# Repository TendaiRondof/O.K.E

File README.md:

# O.K.E
Bereichs übergreifendes Projekt (Optische Kontroll Einheit)

Robo_arm grid = 0.1mm x/Y

cam grid=	0.33mmx
		0.247mmy

Wenn nöd teil vo dem bisch... was machsch den da?

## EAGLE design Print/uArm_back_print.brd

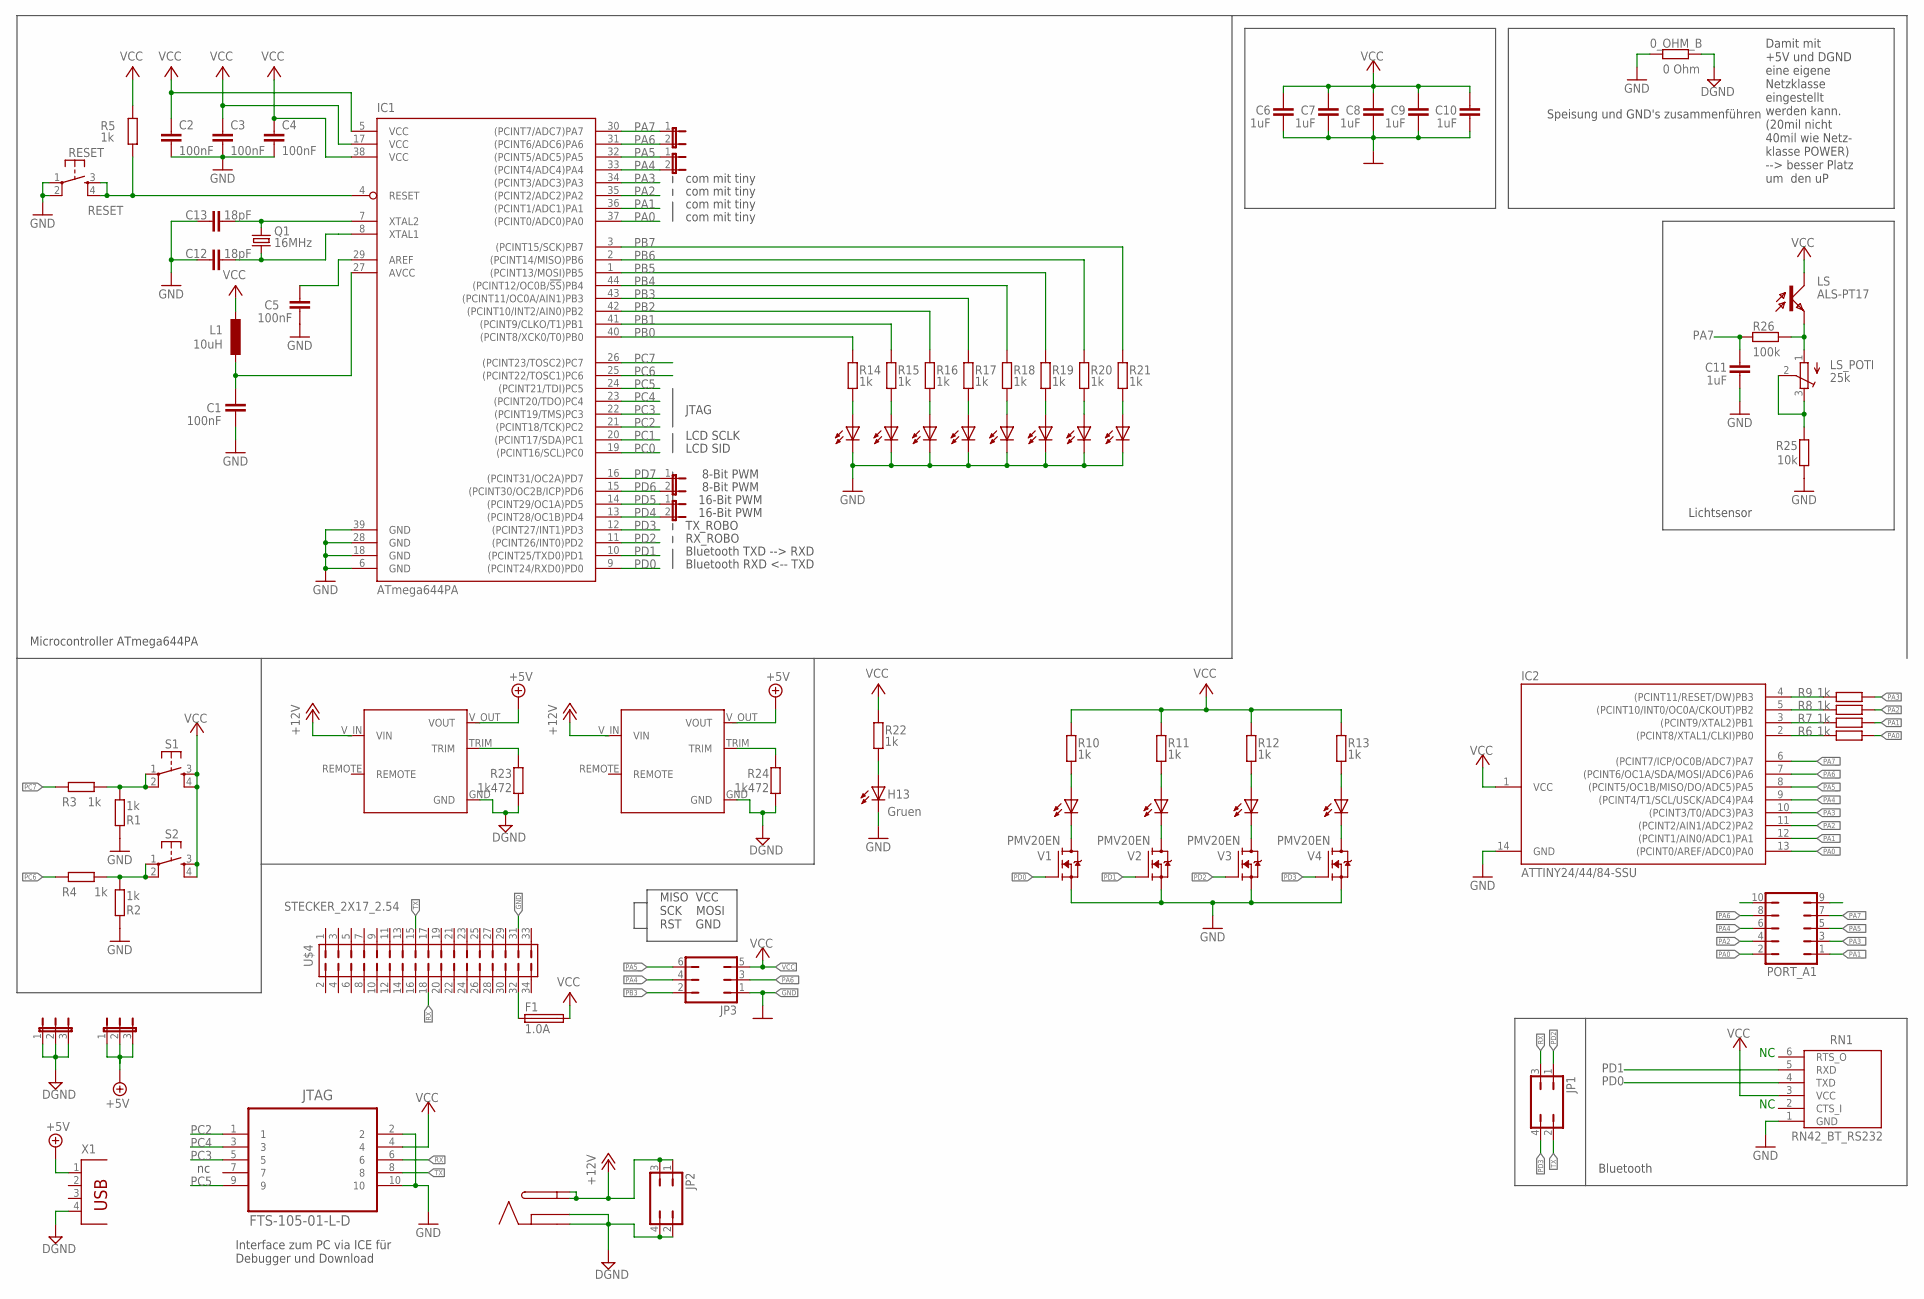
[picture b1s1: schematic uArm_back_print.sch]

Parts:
0_OHM_B: 0 Ohm; R0805
C1, C2, C3, C4, C5: 100nF; C0805
C6, C7, C8, C9, C10, C11: 1uF; C0805
C12, C13: 18pF; C0805
F1: 1.0A; F1206
H1, H2, H3, H4, H5, H6, H7, H8, H9, H10, H11, H12, H13: Gruen; CHIPLED_1206
IC1: ATmega644PA; TQFP44
IC2: ATTINY24/44/84-SSU; SOIC14
IC3, IC4: DCDC; 1X2,3_2.54MM
JP1, JP2: JP2Q
JP3: JP3Q
JP4, JP5, JP8, JP9: JP1
JP6, JP7: JP2E; JP2
JTAG: FTS-105-01-L-D; SAMTEC_FTS-105-01-L-D
L1: 10uH; L2825P
LS: ALS-PT17; SOD232-W
LS_POTI: 25k; 3223G
PORT_A1: JP5Q
Q1: 16MHz; HC49UP
R1, R2, R3, R4, R5, R6, R7, R8, R9, R10, R11, R12, R13, R14, R15, R16, R17, R18, R19, R20, R21, R22: 1k; R0805
R23, R24: 1k472; R0805
R25: 10k; R0805
R26: 100k; R0805
RESET: TS42_4PAD
RN1: RN42_BT_RS232; RN42BT_RS232
S1, S2: TS42_4PAD
U$1: BUCHSE
U$4: STECKER_2X17_2.54; 2X17_2.54
V1, V2, V3, V4: PMV20EN; SOT23
X1: PN87520

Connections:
+5V: IC3.V_OUT (VOUT), IC4.V_OUT (VOUT), JP6.1, JP6.2, JP6.3, X1.1
+12V: IC3.V_IN (VIN), IC4.V_IN (VIN), JP2.1, JP2.3, U$1.3, U$1.3.1
DGND: 0_OHM_B.2, IC3.GND, IC4.GND, JP2.2, JP2.4, JP7.1, JP7.2, JP7.3, R23.1, R24.1, U$1.1, U$1.2, X1.4
GND: 0_OHM_B.1, C1.1, C2.2, C3.2, C4.2, C5.1, C6.1, C7.1, C8.1, C9.1, C10.1, C11.1, C12.2, C13.1, H1.C, H2.C, H3.C, H4.C, H5.C, H6.C, H7.C, H8.C, H13.C, IC1.6 (GND), IC1.18 (GND), IC1.28 (GND), IC1.39 (GND), IC2.14 (GND), JP3.1, JTAG.2, JTAG.10, R1.1, R2.1, R25.1, RESET.1, RESET.2, RN1.1 (GND), U$4.31, V1.2 (S), V2.2 (S), V3.2 (S), V4.2 (S)
unnamed: F1.1, U$4.32
unnamed: H10.C, V2.3 (D)
unnamed: H9.C, V1.3 (D)
unnamed: H10.A, R11.1
unnamed: H9.A, R10.1
unnamed: LS.E, LS_POTI.1 (A), R26.2
unnamed: LS_POTI.2 (S), LS_POTI.3 (E), R25.2
unnamed: H12.C, V4.3 (D)
unnamed: H1.A, R14.1
unnamed: H12.A, R13.1
unnamed: H11.A, R12.1
unnamed: H11.C, V3.3 (D)
unnamed: H2.A, R15.1
unnamed: H3.A, R16.1
unnamed: IC3.TRIM, R23.2
unnamed: H4.A, R17.1
unnamed: H5.A, R18.1
unnamed: H6.A, R19.1
unnamed: H7.A, R20.1
unnamed: R1.2, R3.2, S1.1, S1.2
unnamed: R2.2, R4.2, S2.1, S2.2
unnamed: H8.A, R21.1
unnamed: C1.2, IC1.27 (AVCC), L1.2
unnamed: C12.1, IC1.8 (XTAL1), Q1.1
unnamed: C13.2, IC1.7 (XTAL2), Q1.2
unnamed: C5.2, IC1.29 (AREF)
unnamed: H13.A, R22.1
unnamed: IC4.TRIM, R24.2
PA0: IC1.37 ((PCINT0/ADC0)PA0), R6.1
PA0_: IC2.13 ((PCINT0/AREF/ADC0)PA0), PORT_A1.2
PA1: IC1.36 ((PCINT1/ADC1)PA1), R7.1
PA1_: IC2.12 ((PCINT1/AIN0/ADC1)PA1), PORT_A1.1
PA2: IC1.35 ((PCINT2/ADC2)PA2), R8.1
PA2_: IC2.11 ((PCINT2/AIN1/ADC2)PA2), PORT_A1.4
PA3: IC1.34 ((PCINT3/ADC3)PA3), R9.1
PA3_: IC2.10 ((PCINT3/T0/ADC3)PA3), PORT_A1.3
PA4: IC1.33 ((PCINT4/ADC4)PA4), JP9.2
PA4_: IC2.9 ((PCINT4/T1/SCL/USCK/ADC4)PA4), JP3.4, PORT_A1.6
PA5: IC1.32 ((PCINT5/ADC5)PA5), JP9.1
PA5_: IC2.8 ((PCINT5/OC1B/MISO/DO/ADC5)PA5), JP3.6, PORT_A1.5
PA6: IC1.31 ((PCINT6/ADC6)PA6), JP8.2
PA6_: IC2.7 ((PCINT6/OC1A/SDA/MOSI/ADC6)PA6), JP3.3, PORT_A1.8
PA7: C11.2, IC1.30 ((PCINT7/ADC7)PA7), JP8.1, R26.1
PA7_: IC2.6 ((PCINT7/ICP/OC0B/ADC7)PA7), PORT_A1.7
PB0: IC1.40 ((PCINT8/XCK0/T0)PB0), R14.2
PB0_: IC2.2 ((PCINT8/XTAL1/CLKI)PB0), R6.2
PB1: IC1.41 ((PCINT9/CLKO/T1)PB1), R15.2
PB1_: IC2.3 ((PCINT9/XTAL2)PB1), R7.2
PB2: IC1.42 ((PCINT10/INT2/AIN0)PB2), R16.2
PB2_: IC2.5 ((PCINT10/INT0/OC0A/CKOUT)PB2), R8.2
PB3: IC1.43 ((PCINT11/OC0A/AIN1)PB3), R17.2
PB3_: IC2.4 ((PCINT11/RESET/DW)PB3), JP3.2, R9.2
PB4: IC1.44 ((PCINT12/OC0B/!SS!)PB4), R18.2
PB5: IC1.1 ((PCINT13/MOSI)PB5), R19.2
PB6: IC1.2 ((PCINT14/MISO)PB6), R20.2
PB7: IC1.3 ((PCINT15/SCK)PB7), R21.2
PC0: IC1.19 ((PCINT16/SCL)PC0)
PC1: IC1.20 ((PCINT17/SDA)PC1)
PC2: IC1.21 ((PCINT18/TCK)PC2), JTAG.1
PC3: IC1.22 ((PCINT19/TMS)PC3), JTAG.5
PC4: IC1.23 ((PCINT20/TDO)PC4), JTAG.3
PC5: IC1.24 ((PCINT21/TDI)PC5), JTAG.9
PC6: IC1.25 ((PCINT22/TOSC1)PC6), R4.1
PC7: IC1.26 ((PCINT23/TOSC2)PC7), R3.1
PD0: IC1.9 ((PCINT24/RXD0)PD0), RN1.4 (TXD), V1.1 (G)
PD1: IC1.10 ((PCINT25/TXD0)PD1), RN1.5 (RXD), V2.1 (G)
PD2: IC1.11 ((PCINT26/INT0)PD2), JP1.1, V3.1 (G)
PD3: IC1.12 ((PCINT27/INT1)PD3), JP1.4, V4.1 (G)
PD4: IC1.13 ((PCINT28/OC1B)PD4), JP4.2
PD5: IC1.14 ((PCINT29/OC1A)PD5), JP4.1
PD6: IC1.15 ((PCINT30/OC2B/ICP)PD6), JP5.2
PD7: IC1.16 ((PCINT31/OC2A)PD7), JP5.1
RESET: IC1.4 (RESET), R5.1, RESET.3, RESET.4
RX: JP1.3, JTAG.6, U$4.18
TX: JP1.2, JTAG.8, U$4.15
VCC: C2.1, C3.1, C4.1, C6.2, C7.2, C8.2, C9.2, C10.2, F1.2, IC1.5 (VCC), IC1.17 (VCC), IC1.38 (VCC), IC2.1 (VCC), JP3.5, JTAG.4, L1.1, LS.C, R5.2, R10.2, R11.2, R12.2, R13.2, R22.2, RN1.3 (VCC), S1.3, S1.4, S2.3, S2.4

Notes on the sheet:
JTAG
16-Bit PWM
8-Bit PWM
Interface zum PC via ICE für Debugger und Download
Microcontroller ATmega644PA
LCD SID
LCD SCLK
Bluetooth
Bluetooth RXD <-- TXD
Bluetooth TXD --> RXD
Speisung und GND's zusammenführen
Damit mit +5V und DGND eine eigene Netzklasse eingestellt werden kann. (20mil nicht 40mil wie Netz- klasse POWER) --> besser Platz um den uP
RX_ROBO
TX_ROBO
com mit tiny
MISO VCC SCK MOSI RST GND
Lichtsensor

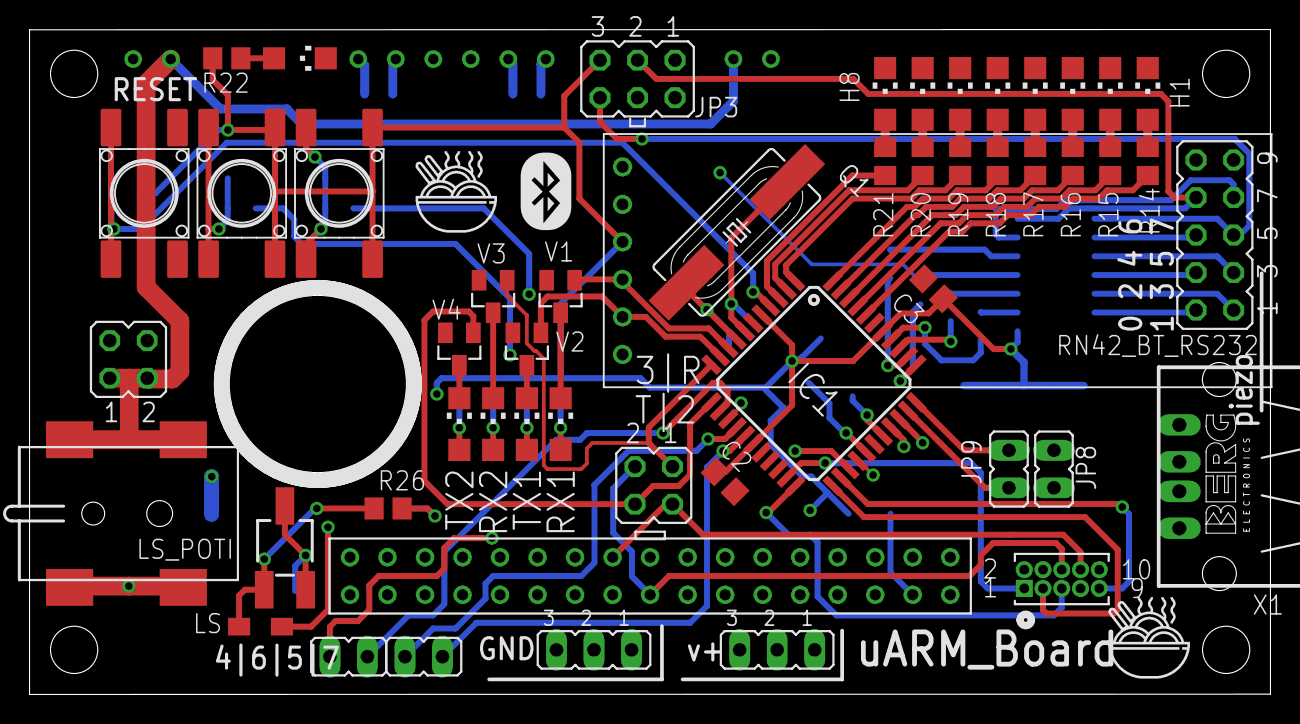
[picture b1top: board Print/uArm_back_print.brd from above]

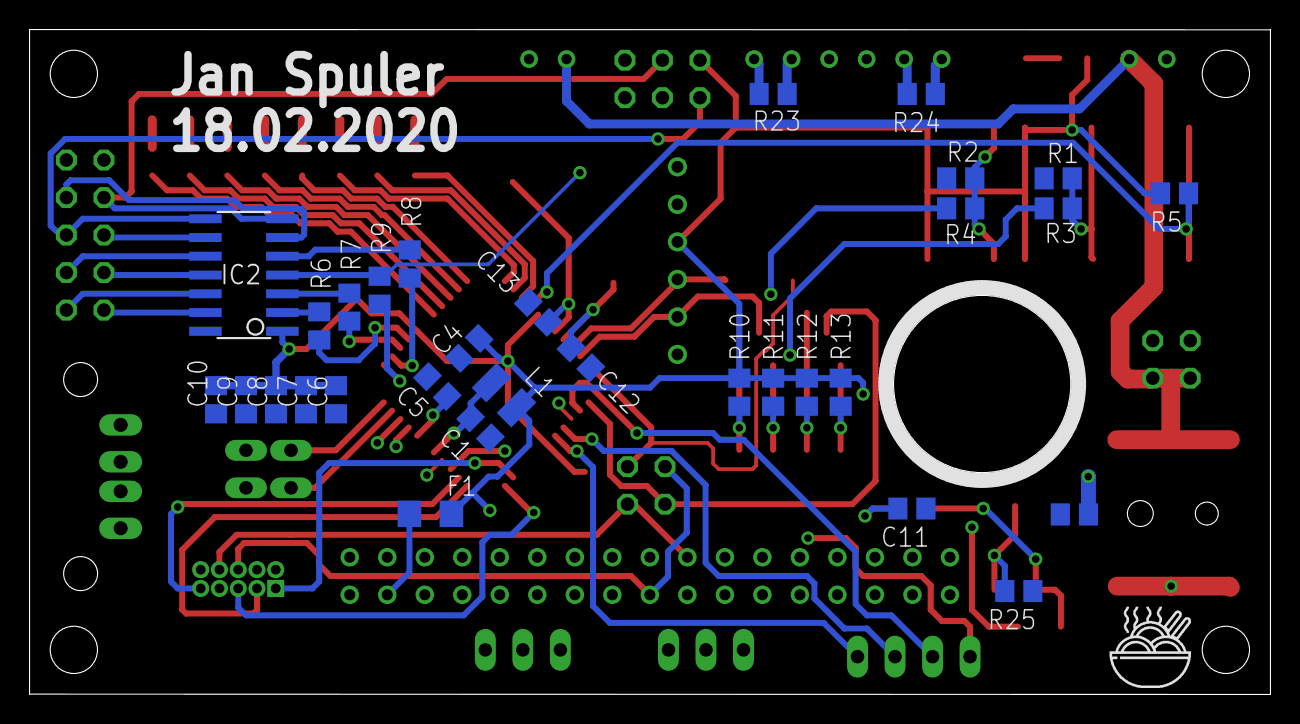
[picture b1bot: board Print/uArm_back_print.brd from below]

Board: 4 copper layers, 84.0 x 45.0 mm, 84 parts (31 on the bottom side), 78 nets.

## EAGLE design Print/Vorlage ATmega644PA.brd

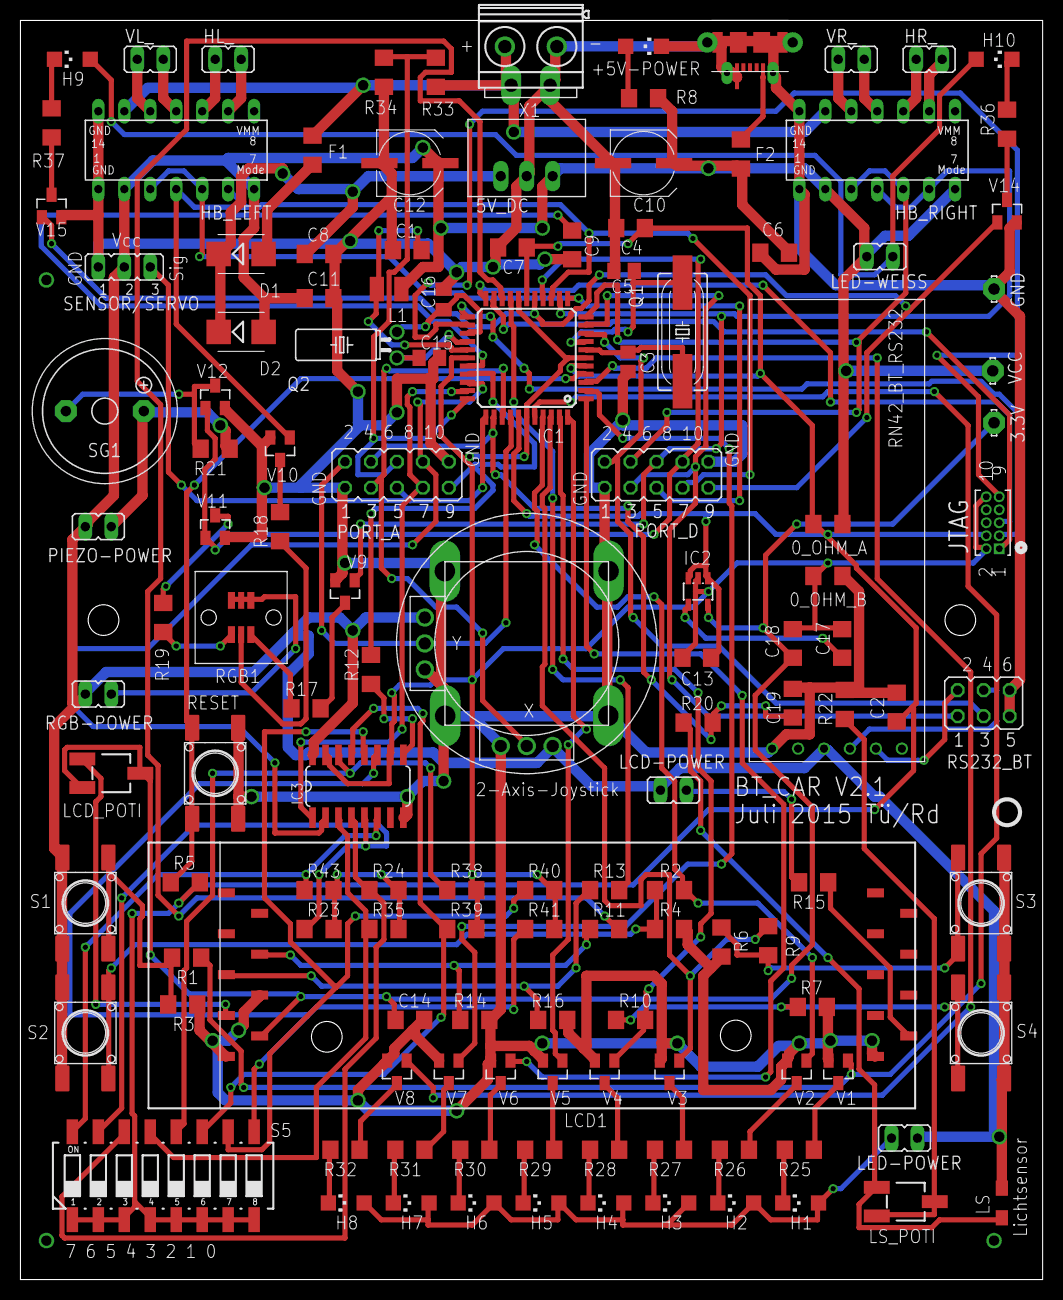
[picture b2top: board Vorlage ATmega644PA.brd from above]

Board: 2 copper layers, 100.0 x 123.2 mm, 134 parts (0 on the bottom side), 109 nets.

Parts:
0_OHM_A, 0_OHM_B: 0 Ohm; R1206
3.3V: 3.3V; LSP11
5V_DC: RECOM_DCDC
+5V-POWER: Gruen; CHIPLED_1206
C1, C2, C4, C6, C7, C8, C9, C11, C14, C17: 100nF; C1206
C3: 18pF; C0805
C5: 18pF; C0805K
C10, C12: 100uF; UD-6,3X5,8_NICHICON
C13, C18, C19: 1uF; C1206
C15, C16: 12pF; C0805K
D1, D2: MBRS130LT3; SMB
F1: 1.0A; F1206
F2: 500mA; F1206
GND: 3.3V; LSP11
H1, H3, H5, H7: rot; CHIPLED_1206
H2, H4, H6, H8: blau; CHIPLED_1206
H9, H10: weiss; CHIPLED_1206
HB_LEFT: DRV8835; DIL14
HB_RIGHT: DRV8835; DIL14
HL_: JP1
HR_: JP1
IC1: ATmega644PA; TQFP44
IC2: LP2985-XXDBVR; SOT23-DBV
IC3: 74AC165D; SO16
JTAG: FTS-105-01-L-D; SAMTEC_FTS-105-01-L-D
L1: 10uH; L2825P
LCD1: EADIP203-4_SMD; EADIP203-4SMD
LCD-POWER: JP1
LCD_POTI: 2k5; 3223G
LED-POWER: JP1
LED-WEISS: JP1
LS: ALS-PT17; SOD232-W
LS_POTI: 25k; 3223G
PIEZO-POWER: JP1
PORT_A: JP5Q
PORT_D: JP5Q
Q1: 16MHz; HC49UP
Q2: 32.768kHz; TC38H
R1, R2, R8, R9, R10, R11, R12, R13, R21: 1k; R1206
R3, R4, R6, R7, R20, R23, R24, R33, R34, R35, R38, R39, R40, R41, R43: 100k; R1206
R5, R22: 10k; R1206
R14, R16: 2k; R1206
R15, R17, R18, R19, R25, R26, R27, R28, R29, R30, R31, R32, R36, R37: 150R; R1206
RESET: TS42_4PAD
RGB1: LED_MIT_DIFUSOR
RGB-POWER: JP1
RN1: RN42_BT_RS232; RN42BT_RS232
RS232_BT: JP3Q
S1, S2, S3, S4: TS42_4PAD
S5: 219-08; CTS-219-08
SENSOR/SERVO: JP2
SG1: F/TMB
U$1: MICRO-USB; 47589-0001
U$6: 2-AXIS-JOYSTICK
V1, V2, V3, V4, V5, V6, V7, V8, V9, V10, V11, V12, V14, V15: PMV20EN; SOT23
VCC: 3.3V; LSP11
VL_: JP1
VR_: JP1
X1: MKDSN1,5/2-5,08

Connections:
3.3V: 3.3V.MP, C14.1, C18.1, IC2.5, LCD1.2, LCD_POTI.2, LCD_POTI.3
+5V: 0_OHM_A.2, C2.1, C4.1, C7.1, C13.1, IC1.5, IC1.17, IC1.38, IC2.1, IC2.3, JTAG.4, R5.2, S5.1, S5.2, S5.3, S5.4, S5.5, S5.6, S5.7, S5.8
DGND: 0_OHM_B.2, C13.2, C17.2, C18.2, IC1.6, IC1.18, IC1.28, IC1.39, IC2.2, IC3.10, IC3.15, JTAG.2, JTAG.10, R23.2, R24.2, R35.2, R38.2, R39.2, R40.2, R41.2, R43.2
GND: 0_OHM_B.1, 5V_DC.GND, +5V-POWER.C, C1.1, C2.2, C3.1, C4.2, C5.2, C6.2, C7.2, C8.2, C9.1, C10.-, C11.2, C12.-, C14.2, C15.2, C16.2, C19.1, GND.MP, HB_LEFT.1, HB_LEFT.14, HB_RIGHT.1, HB_RIGHT.14, IC3.8, LCD1.1, LCD1.4, LCD1.18, PORT_A.1, PORT_A.10, PORT_D.1, PORT_D.10, R3.1, R4.1, R6.2, R7.2, R14.1, R16.1, R22.1, R34.1, RESET.1, RESET.2, RN1.1, RS232_BT.5, RS232_BT.6, SENSOR/SERVO.1, U$1.5, U$1.CASING1, U$1.CASING2, U$1.CASING3, U$1.CASING4, U$1.CASING5, U$1.CASING6, U$1.CASING7, U$1.CASING8, U$6.CASE1, U$6.CASE2, U$6.CASE3, U$6.CASE4, U$6.L/R-, U$6.U/D-, V1.2, V2.2, V3.2, V4.2, V5.2, V6.2, V7.2, V8.2, V9.2, V10.2, V11.2, V12.2, V14.2, V15.2, X1.1.1, X1.1.2
unnamed: R19.2, RGB1.1
unnamed: R18.2, RGB1.2
unnamed: F2.1, U$1.1
unnamed: H9.A, H10.A, LED-WEISS.2
unnamed: H2.C, R26.2
unnamed: H1.C, R25.2
unnamed: R25.1, V1.3
unnamed: R26.1, V2.3
unnamed: D1.A, F1.2
unnamed: H10.C, R36.2
unnamed: R17.2, RGB1.3
unnamed: LCD-POWER.2, R15.2
unnamed: H1.A, H2.A, H3.A, H4.A, H5.A, H6.A, H7.A, H8.A, LED-POWER.2
unnamed: RN1.5, RS232_BT.2
unnamed: RN1.4, RS232_BT.4
unnamed: R21.2, SG1.-, V12.3
unnamed: IC3.6, R43.1, S5.16
unnamed: IC3.5, R23.1, S5.15
unnamed: LS.E, LS_POTI.1, R20.2
unnamed: LS_POTI.2, LS_POTI.3, R22.2
unnamed: R1.2, R3.2, S1.1, S1.2
unnamed: R2.2, R4.2, S2.1, S2.2
unnamed: R7.1, R10.1, S4.3, S4.4
unnamed: R6.1, R9.1, S3.3, S3.4
unnamed: H4.C, R28.2
unnamed: H3.C, R27.2
unnamed: R17.1, V9.3
unnamed: R18.1, V10.3
unnamed: R19.1, V11.3
unnamed: R27.1, V3.3
unnamed: IC3.4, R24.1, S5.14
unnamed: R28.1, V4.3
unnamed: H9.C, R37.2
unnamed: LCD1.3, LCD_POTI.1
unnamed: C1.2, IC1.27, L1.2
unnamed: C5.1, IC1.8, Q1.1
unnamed: C3.2, IC1.7, Q1.2
unnamed: C9.2, IC1.29
unnamed: LCD1.6, R11.1, R14.2
unnamed: LCD1.5, R13.1, R16.2
unnamed: R37.1, V15.3
unnamed: H6.C, R30.2
unnamed: H5.C, R29.2
unnamed: R29.1, V5.3
unnamed: R30.1, V6.3
unnamed: R36.1, V14.3
unnamed: HB_LEFT.12, VL_.1
unnamed: H8.C, R32.2
unnamed: H7.C, R31.2
unnamed: R31.1, V7.3
unnamed: R32.1, V8.3
unnamed: HB_LEFT.11, VL_.2
unnamed: HB_LEFT.10, HL_.1
unnamed: HB_LEFT.9, HL_.2
unnamed: HB_RIGHT.12, VR_.1
unnamed: HB_RIGHT.11, VR_.2
unnamed: HB_RIGHT.10, HR_.1
unnamed: HB_RIGHT.9, HR_.2
unnamed: IC3.3, R35.1, S5.13
unnamed: +5V-POWER.A, R8.1
unnamed: IC3.14, R38.1, S5.12
unnamed: IC3.13, R39.1, S5.11
unnamed: IC3.12, R40.1, S5.10
unnamed: IC3.11, R41.1, S5.9
unnamed: PIEZO-POWER.2, R21.1, SG1.+
unnamed: IC3.9, R12.1
unnamed: C17.1, IC2.4
unnamed: 5V_DC.IN, C8.1, D1.C, D2.C
unnamed: RGB1.4, RGB1.5, RGB1.6, RGB-POWER.2
unnamed: LCD1.17, R15.1
PA0: IC1.37, PORT_A.2, U$6.U/D_M
PA1: IC1.36, PORT_A.3, U$6.L/R_M
PA2: C19.2, IC1.35, PORT_A.4, R20.1
PA3: IC1.34, PORT_A.5, SENSOR/SERVO.3
PA4: IC1.33, PORT_A.6, R33.1, R34.2
PA5: IC1.32, IC3.1, PORT_A.7
PA6: IC1.31, IC3.2, PORT_A.8
PA7: IC1.30, PORT_A.9, R12.2
PB0: IC1.40, R1.1, V1.1
PB1: IC1.41, R2.1, V2.1
PB2: IC1.42, R9.2, V3.1
PB3: IC1.43, R10.2, V4.1
PB4: IC1.44, V5.1
PB5: IC1.1, V6.1
PB6: IC1.2, V7.1
PB7: IC1.3, V8.1
PC0: IC1.19, R13.2
PC1: IC1.20, R11.2
PC2: IC1.21, JTAG.1
PC3: IC1.22, JTAG.5
PC4: IC1.23, JTAG.3
PC5: IC1.24, JTAG.9
PC6: C16.1, IC1.25, Q2.2
PC7: C15.1, IC1.26, Q2.1
PD0: IC1.9, PORT_D.2, RS232_BT.3
PD1: IC1.10, PORT_D.3, RS232_BT.1
PD2: HB_RIGHT.3, HB_RIGHT.5, IC1.11, PORT_D.4
PD3: HB_LEFT.3, HB_LEFT.5, IC1.12, PORT_D.5
PD4: HB_RIGHT.4, HB_RIGHT.6, IC1.13, PORT_D.6, V9.1
PD5: HB_LEFT.4, HB_LEFT.6, IC1.14, PORT_D.7, V10.1
PD6: IC1.15, PORT_D.8, V11.1, V12.1
PD7: IC1.16, PORT_D.9, V14.1, V15.1
RESET: IC1.4, R5.1, RESET.3, RESET.4
VCC: 0_OHM_A.1, 5V_DC.OUT, C6.1, C10.+, C11.1, C12.+, D2.A, F2.2, HB_LEFT.2, HB_LEFT.7, HB_RIGHT.2, HB_RIGHT.7, IC3.16, L1.1, LCD-POWER.1, LED-POWER.1, LED-WEISS.1, LS.C, PIEZO-POWER.1, R8.2, RGB-POWER.1, RN1.3, S1.3, S1.4, S2.3, S2.4, S3.1, S3.2, S4.1, S4.2, SENSOR/SERVO.2, U$6.L/R+, U$6.U/D+, VCC.MP
V_AKKU: F1.1, HB_LEFT.13, HB_RIGHT.13, R33.2, X1.2.1, X1.2.2

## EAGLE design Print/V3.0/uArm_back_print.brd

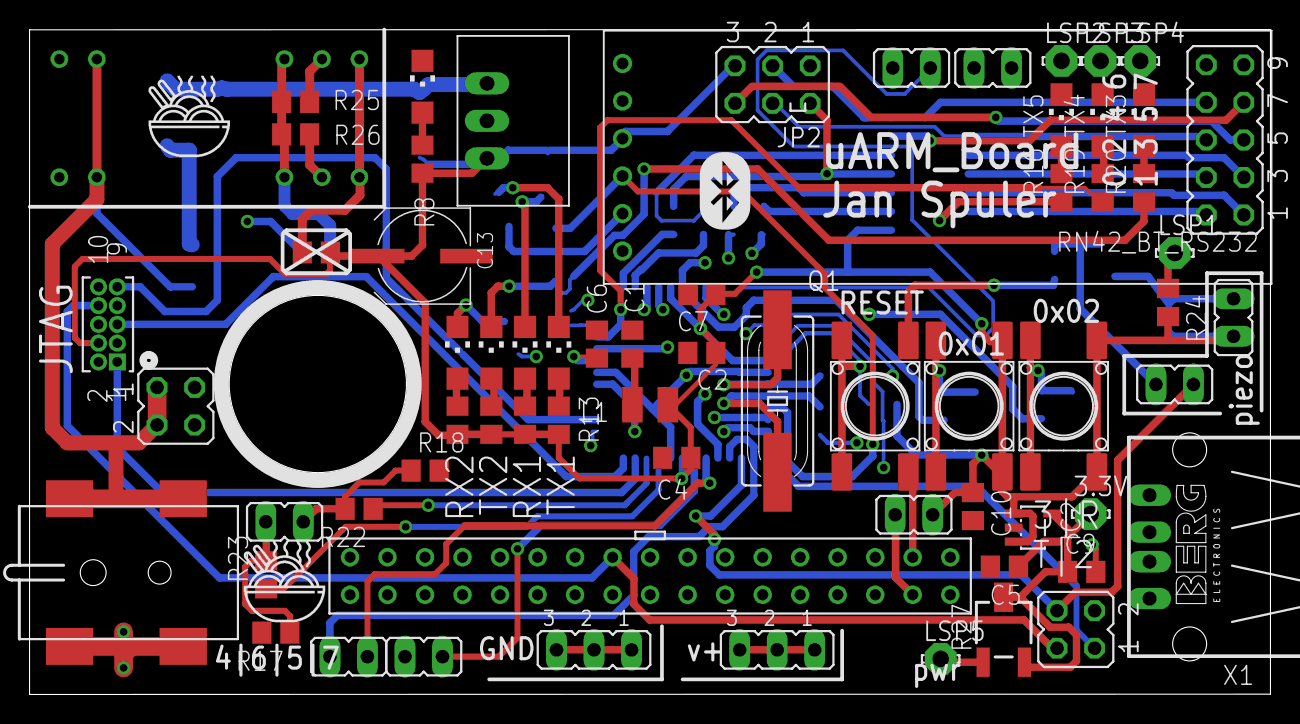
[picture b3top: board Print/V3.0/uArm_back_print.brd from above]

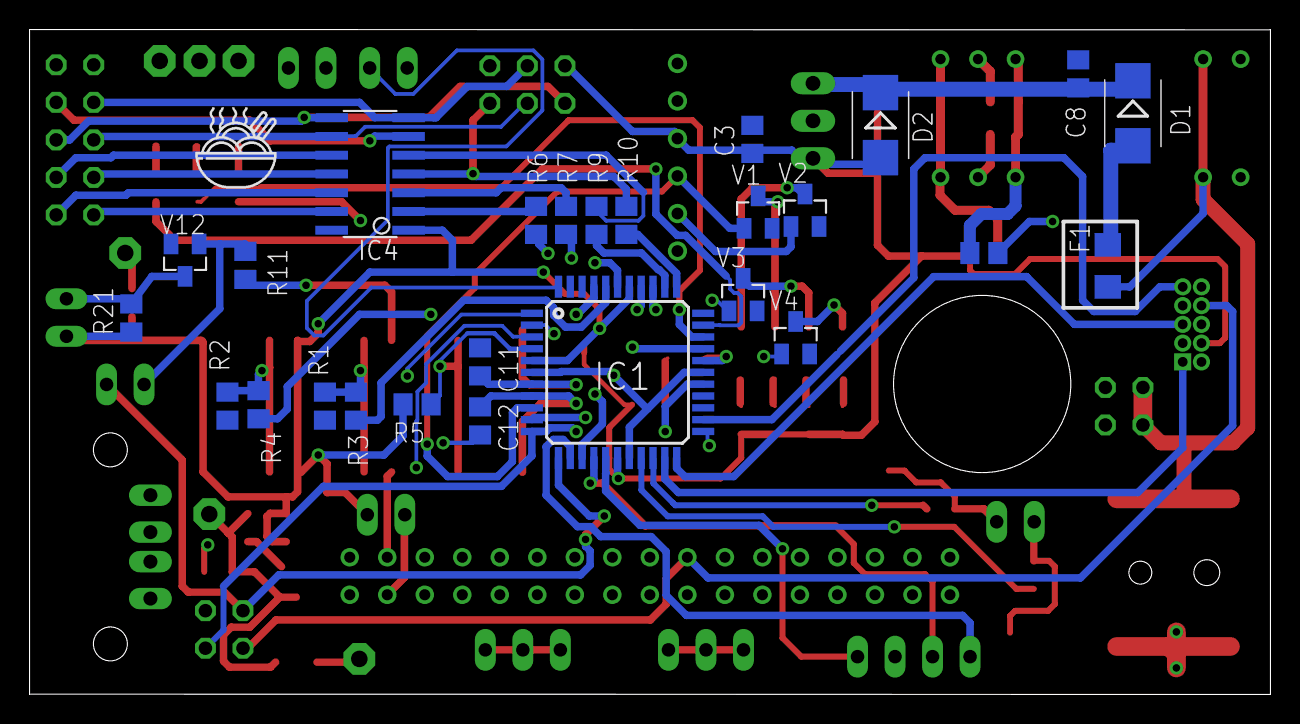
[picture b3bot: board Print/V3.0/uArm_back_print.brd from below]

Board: 4 copper layers, 84.0 x 45.0 mm, 94 parts (26 on the bottom side), 78 nets.

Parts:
0_OHM_A, 0_OHM_B: 0 Ohm; R0805
3.3V: 3.3V; LSP11
5V_DC: RECOM_DCDC
+5V-POWER: Gruen; CHIPLED_1206
C1, C2, C3, C4, C5, C6, C7, C8: 100nF; C0805
C9, C10: 1uF; C0805
C11, C12: 18pF; C0805
C13: 100uF; UD-6,3X5,8_NICHICON
D1, D2: MBRS130LT3; SMB
F1: 1.0A; F1206
IC1: ATmega644PA; TQFP44
IC2: LP2985-XXDBVR; SOT23-DBV
IC4: ATTINY24/44/84-SSU; SOIC14
JP1, JP3: JP2Q
JP2: JP3Q
JTAG: FTS-105-01-L-D; SAMTEC_FTS-105-01-L-D
L1: 10uH; L2825P
LSP1, LSP2, LSP3, LSP4, LSP5: LSP11
PIEZO-POWER1, PIEZO-POWER2, PIEZO-POWER3, PIEZO-POWER4, PIEZO-POWER5, PIEZO-POWER8, PIEZO-POWER9, PIEZO-POWER10: JP1
PORT_A1: JP5Q
Q1: 16MHz; HC49UP
R1, R2: 100k; R0805
R3, R4, R5, R8, R11, R12, R13, R14, R15, R16, R17, R18, R19, R20, R21, R22, R23, R24: 1k; R0805
R6, R7, R9, R10: 150R; R0805
R25, R26: 1k472; R0805
R27: 3223G
RESET: TS42_4PAD
RN1: RN42_BT_RS232; RN42BT_RS232
RX1, RX2: Gruen; CHIPLED_1206
S1, S2: TS42_4PAD
TX1, TX2, TX3, TX4, TX5: Gruen; CHIPLED_1206
U$1: BUCHSE
U$2, U$3: DCDC; 1X2,3_2.54MM
U$4: STECKER_2X17_2.54; 2X17_2.54
UART_ROBO1, UART_ROBO2: JP2
V1, V2, V3, V4, V12: PMV20EN; SOT23
X1: PN87520

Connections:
3.3V: 3.3V.MP, C9.1, IC2.5, R27.2, R27.3
+5V: 0_OHM_A.2, U$2.V_OUT, U$3.V_OUT, UART_ROBO1.1, UART_ROBO1.2, UART_ROBO1.3, X1.1
+12V: F1.1, JP3.1, JP3.3, U$1.3, U$1.3.1, U$2.V_IN, U$3.V_IN
DGND: 0_OHM_B.2, IC1.6, IC1.18, IC1.28, IC1.39, JP3.2, JP3.4, R25.1, R26.1, U$1.1, U$1.2, U$2.GND, U$3.GND, UART_ROBO2.1, UART_ROBO2.2, UART_ROBO2.3, X1.4
GND: 0_OHM_B.1, 5V_DC.GND, +5V-POWER.C, C1.1, C2.2, C3.2, C4.2, C5.2, C6.1, C7.2, C8.2, C9.2, C10.2, C11.1, C12.2, C13.-, IC2.2, IC4.14, JP2.1, JTAG.2, JTAG.10, LSP2.MP, LSP3.MP, LSP4.MP, R1.1, R2.1, R11.2, R17.2, R18.2, RESET.1, RESET.2, RN1.1, TX3.C, TX4.C, TX5.C, U$4.31, V1.2, V2.2, V3.2, V4.2, V12.2
unnamed: PIEZO-POWER4.2, U$4.32
unnamed: TX1.C, V2.3
unnamed: RX1.C, V1.3
unnamed: R13.1, TX1.A
unnamed: R12.1, RX1.A
unnamed: R16.2, TX5.A
unnamed: R19.2, TX4.A
unnamed: RX2.C, V4.3
unnamed: D1.A, F1.2
unnamed: R15.1, RX2.A
unnamed: R14.1, TX2.A
unnamed: TX2.C, V3.3
unnamed: R20.2, TX3.A
unnamed: PIEZO-POWER10.2, R18.1, R22.2
unnamed: PIEZO-POWER10.1, R17.1, R23.2
unnamed: R26.2, U$3.TRIM
unnamed: LSP5.MP, R27.1
unnamed: LSP1.MP, R24.1
unnamed: R1.2, R3.2, S1.1, S1.2
unnamed: R2.2, R4.2, S2.1, S2.2
unnamed: C1.2, IC1.27, L1.2
unnamed: C12.1, IC1.8, Q1.1
unnamed: C11.2, IC1.7, Q1.2
unnamed: C6.2, IC1.29
unnamed: PIEZO-POWER2.2, R21.2, V12.3
unnamed: +5V-POWER.A, R8.1
unnamed: C5.1, IC2.4
unnamed: 5V_DC.IN, C8.1, D1.C, D2.C
unnamed: R25.2, U$2.TRIM
PA0: IC1.37, R6.1
PA0_: IC4.13, PORT_A1.2
PA1: IC1.36, R7.1
PA1_: IC4.12, PORT_A1.1
PA2: IC1.35, R9.1
PA2_: IC4.11, PORT_A1.4
PA3: IC1.34, R10.1
PA3_: IC4.10, PORT_A1.3
PA4_: IC4.9, JP2.4, PORT_A1.6
PA5: IC1.32, R20.1
PA5_: IC4.8, JP2.6, PORT_A1.5
PA6: IC1.31, R19.1
PA6_: IC4.7, JP2.3, PORT_A1.8
PA7: IC1.30, R16.1
PA7_: IC4.6, PORT_A1.7
PB0: IC1.40, R3.1
PB0_: IC4.2, R6.2
PB1: IC1.41, R4.1
PB1_: IC4.3, R7.2
PB2_: IC4.5, R9.2
PB3_: IC4.4, JP2.2, R10.2
PB4: IC1.44, PIEZO-POWER9.1
PB5: IC1.1, PIEZO-POWER9.2
PB6: IC1.2, PIEZO-POWER8.1
PB7: IC1.3, PIEZO-POWER8.2
PC0: IC1.19, R23.1
PC1: IC1.20, R22.1
PC2: IC1.21, JTAG.1
PC3: IC1.22, JTAG.5
PC4: IC1.23, JTAG.3
PC5: IC1.24, JTAG.9
PD0: IC1.9, RN1.4, V1.1
PD1: IC1.10, RN1.5, V2.1
PD2: IC1.11, JP1.1, V3.1
PD3: IC1.12, JP1.4, PIEZO-POWER1.1, V4.1
PD4: IC1.13, PIEZO-POWER3.1
PD5: IC1.14, PIEZO-POWER5.2
PD6: IC1.15, PIEZO-POWER3.2
PD7: IC1.16, PIEZO-POWER5.1
PD8: PIEZO-POWER1.2, R11.1, V12.1
RESET: IC1.4, R5.1, RESET.3, RESET.4
RX: JP1.3, JTAG.6, U$4.18
TX: JP1.2, JTAG.8, U$4.15
VCC: 0_OHM_A.1, 5V_DC.OUT, C2.1, C3.1, C4.1, C7.1, C10.1, C13.+, D2.A, IC1.5, IC1.17, IC1.38, IC2.1, IC2.3, IC4.1, JP2.5, JTAG.4, L1.1, PIEZO-POWER2.1, PIEZO-POWER4.1, R5.2, R8.2, R12.2, R13.2, R14.2, R15.2, R21.1, R24.2, RN1.3, S1.3, S1.4, S2.3, S2.4

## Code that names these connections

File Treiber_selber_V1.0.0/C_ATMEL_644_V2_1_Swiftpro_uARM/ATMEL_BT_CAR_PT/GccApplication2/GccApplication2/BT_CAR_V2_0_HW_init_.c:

/*************************************************************************** 
    MSW-Winterthur Berufsfachschule, Zeughausstrasse 56, 8400 Winterthur     
    ---------------------------------------------------------------------    
    File        : sirius_driver.c
    Datum       : 1.4.2015
    Version			:	1.00
    Beschreibung: HW-Treiber für BT_CAR_V2_0
    Hardware    : ATMEGA644
    Autor  			:	Ch. Riedel

****************************************************************************
    History
  		5.4.2015	: 1. Version erstellt	(ri)

****************************************************************************/

#include <avr/io.h>
#include <avr/interrupt.h>
#include "BT_CAR_V2_0.h"
#include <avr/pgmspace.h>							// Ermöglicht die Platzierung von "static const" im Code-Segment, statt im RAM.
													// Definition mit "PROGMEM", Lesen mit "pgm_read_byte, pgm_read_ptr"
																		
#pragma GCC optimize 0								// Optimierung ausschalten, damit das Debugging möglich ist

void LED_Show(void)
{
	u8 i;
	
	PORTB=0x01;
	for(i=0;i<8;i++)
	{
		wait_1ms(50);
		PORTB=0x01<<i;
	}
	PORTB=0x80;
	for(i=0;i<8;i++)
	{
		wait_1ms(50);
		PORTB=0x80>>i;
	}
	wait_1ms(100);
	PORTB=0x00;	
}

void init_BT_CAR_V2_0(void)
{
	// Initialisierung PortA
	DDRA  = 0x60;			// Eingang PA0..PA4 as Input (analog Signals), PA5 and PA6 as Output and PA7 as Input (SRG Ansteuerung)

	//Initialisierung Port B
	DDRB  =  0xFF;			// LED Port, alles Outputs, ACHTUNG PB.0...PB.3 sind auch Taster am LCD Display

	//Initialisierung Port C
	//PC0, PC1 im LCD Driver definiert
	//PC2...PC5 für JTAG Schnittstelle
	//PC6, PC7 32.678 KHz Quarz 

	//Initialisierung PortD
	DDRD  =  0xFC;			// PD7,PD6,PD5,PD4 als Outputs (PWM), PD3 Output (Enable HB), PD2 Output (Summer)
							// PD1 und PD0 sind TxD und RxD von UART0 werden über RXEN und TXEN aktiviert
							
	sei(); 					// Global Interrupts aktivieren	
	lcd_init();				// Das LCD muss ebenfalls initialisiert werden, um später genutz werden zu können
	clear_lcd();
	//write_text(0, 0,PSTR("LCD init ok"));
	LED_Show();							
}

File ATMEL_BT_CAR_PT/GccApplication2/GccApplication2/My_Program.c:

/*************************************************************************** 
    MSW-Winterthur Berufsfachschule, Zeughausstrasse 56, 8400 Winterthur     
    ---------------------------------------------------------------------    
	Bluetooth CAR V21
    Datum       : 7.7.2015
    Version		: 2.1
    Beschreibung: Demo Projekt für das Board BT_CAR_V21, Microprozessor TMEL644PA
    Autor  		: Peter Trüb, LCD Treiber Christian Riedel

****************************************************************************/

#include <avr/io.h>
#include <avr/interrupt.h>
#include "BT_CAR_V2_0.h"
#include <avr/pgmspace.h>							// Ermöglicht die Platzierung von "static const" im Code-Segment, statt im RAM.
													// Definition mit "PROGMEM", Lesen mit "pgm_read_byte, pgm_read_ptr"
																			
#pragma GCC optimize 0								// Optimierung ausschalten, damit das Debugging möglich ist

#define JOYSTICK_X 0
#define JOYSTICK_Y 1
#define LICHTSENSOR 2
#define DIP_SWITCH 8

u8 DIP_Switch, LCD_Taster,Receive_count=0,i=0;
u8 Data_Array[50];
unsigned char PWM_Right;
unsigned char PWM_Left;

void init_ADC(void)
{
	// Initialisierung des ADC's
	ADCSRA |=  (1 << ADEN);						// A/D-Wandler Enable
	ADMUX  |= (1 << REFS0);						// Vcc als Referenz
	ADCSRA |= (1 << ADPS0) | (1 << ADPS1) | (1 << ADPS2);		// Clock = CPU / 128 ==> ADC_Clock = 125kHz ==> Conversen-Time = 104us
}

u8 get_DIP_Switch(void)
{
	u8 DIP_Result=0;
	int j;
	
	PORTA |= 0x20;	//PA5=High Load
	PORTA &= 0xDF;	//PA5=Low Load
	PORTA |= 0x20;	//PA5=High --> Load an SRG
	
	for (j=7;j>=0;j--)
	{
		DIP_Result = DIP_Result | ((PINA & 0x80) >> (7-j)); //Bit an PA7 einlesen, MSB first
		PORTA &= 0xBF;	//PA6=Low Clk
		PORTA |= 0x40;	//PA6=High --> steigende Flanke an Clk von SRG
	}
	return(DIP_Result);
}

u8 get_LCD_Taster(void)
{
	u8 LCD_Taster;
	
	//Initialisierung Port B
	PORTB &= 0xF0;			//4xNull ausgeben um Eingangskapazität zu "leeren", diese Pins werden im nächsten Befehl zu Eingängen umgeschaltet

	DDRB  =  0xF0;			// PB0...PB3 neu als Inputs (4 Taster)
	asm  ("nop");			//Zeit für Synchronisation
	asm  ("nop");			//Zeit für Synchronisation
	asm  ("nop");			//Zeit für Synchronisation
	asm  ("nop");			//Zeit für Synchronisation
	asm  ("nop");			//Zeit für Synchronisation
	asm  ("nop");			//Zeit für Synchronisation
	asm  ("nop");			//Zeit für Synchronisation
	asm  ("nop");			//Zeit für Synchronisation
	asm  ("nop");			//Zeit für Synchronisation
	asm  ("nop");			//Zeit für Synchronisation
	LCD_Taster = PINB & 0x0F;
	//Initialisierung Port B
	DDRB  =  0xFF;			// jetzt wieder LED Port, alles Outputs
	return(LCD_Taster);
}

u16 get_ADC_Channel(u8 Kanal)
{	u16 AD_Result;
	ADMUX = (ADMUX & 0xF8) | Kanal;	// Die drei Mux Bits löschen und neuen Kanal setzen
	ADCSRA |=  (1 << ADSC);			// Start, Single Mode
	while(ADCSRA & (1 << ADSC))		// Warten, bis Messung fertig ist.
	;
	AD_Result = ADCL + (ADCH << 8);	//	ADCL zuerst lesen und dann erst ADCH !!!
	return(AD_Result);
}

void init_PWM_16Bit_Timer1(void)
{
	//Init TIMER1
	TCCR1A = 0x00;
	TCCR1B = 0x00;
	//Fast PWM 0x000 bis ICR1 --> ok
	TCCR1A |= (1 << WGM11) | (1 << COM1A1) | (1 << COM1B1); //Clear OCnA/OCnB //Pin when Compare Match
	TCCR1B |= (1 << WGM12) | (1 << WGM13) | (1 << CS11); //Fast PWM TOP=ICR1, //16MHz/8--> 1/2MHzx100 // --> 20kHz PWM
	ICR1=100; //PWM TOP --> 20kHz
	OCR1A = 50; //50% PWM
	OCR1B = 50; //50% PWM
	PORTD |= 0x0C; //PD2,PD3, Enable H-Bridge left and right
}

void init_RGB(void)
{
	TCCR1A = 0x00;
	TCCR1B = 0x00;
	TCCR2A = 0x00;
	TCCR2B = 0x00;
	
	//Init TIMER1 16 Bit
	TCCR1A |= (1 << WGM10);
	TCCR1B |= (1 << WGM12); // Fast PWM 8Bit, Top=0xFF
	TCCR1A |= (1 << COM1A1) | (1 << COM1B1);	//Clear OCnA/OCnB Pin when Compare Match
	TCCR1B |= (1 << CS11);	//16MHz/8	--> 1/2MHzx255 --> 7.843kHz PWM Frequenz
	OCR1A = 0;	//Comparewert 1A
	OCR1B = 0;	//Comparewert 1B

	//Init TIMER2 8 Bit
	TCCR2A |= (1 << WGM21) | (1 << WGM20); // Fast PWM 8Bit, Top=0xFF
	TCCR2A |= (1 << COM2B1);	//Clear OCnB Pin when Compare Match
	TCCR2B |= (1 << CS21);	//16MHz/8	--> 1/2MHzx255 --> 7.843kHz PWM Frequenz
	OCR2B = 0;	//Comparewert 2B
}

void init_UART0(void)
{
	// Initialisierung UART0 (RxD0, TxD0)
	UBRR0 = 16;	//Bei 16MHZ und U2X0=1 --> 115k2 Baudrate
	UCSR0A |= (1 << U2X0);
	//UCSR0C muss nicht initialisiert werden, Standardwerte: Asynchron, 8Databits,Noneparity, ein Stopbit
	UCSR0B |= (1 << RXCIE0) | (1 << RXEN0) | (1 << TXEN0); //TxD, RxD Enable und RxD Interrupt Enable
}

void send_Byte(u8 val)
{
	//Wait for empty Buffer
	while( !(UCSR0A & (1<<UDRE0)) )
	;
	
	UDR0=val;	//Transmit starts
}

void Send_USART(u8 Code, u8 value)
{
	u8 Hunderter,Zehner,Einer;
	
	Hunderter=value/100;
	Zehner=(value-Hunderter*100)/10;
	Einer=value-Hunderter*100-Zehner*10;
	
	switch (Code)
	{
		case DIP_SWITCH:	send_Byte('D');
							break;
		case JOYSTICK_X:	send_Byte('X');
							break;						
		case JOYSTICK_Y:	send_Byte('Y');
							break;						
		case LICHTSENSOR:	send_Byte('S');
							break;							
	}
	send_Byte(Hunderter+0x30);
	send_Byte(Zehner+0x30);
	send_Byte(Einer+0x30);
}


ISR (USART0_RX_vect) // UART0 Empfangsinterrupt
{
	unsigned int OCR1A_tmp,OCR1B_tmp;
	// ----------------------- Daten empfangen -------------------------
	Data_Array[i] = UDR0-0x30; //Empfangspuffer lesen, Achtung -0x30!
	if ( (Data_Array[0]+0x30) == 'L') //WICHTIG!!! --> 'L' als Zeichen //abwarten, synchronisieren mit Sender
	i++;
	if (i==8) //i==8 ??String empfangen z.B. L123R207
	{
		i=0; //Bsp: String=L078R231
		//PWM_Left
		PWM_Left=100*Data_Array[1]+10*Data_Array[2]+Data_Array[3];
		OCR1A_tmp=(u16)(PWM_Left/2.55); //Bereich anpassen
		if (OCR1A_tmp>90)
		OCR1A_tmp =90;
		if (OCR1A_tmp<10)
		OCR1A_tmp =10;
		OCR1A=OCR1A_tmp;
		
		//PWM_Right
		PWM_Right=100*Data_Array[5]+10*Data_Array[6]+Data_Array[7];
		OCR1B_tmp=(u16)(PWM_Right/2.55); //Bereich anpassen
		if (OCR1B_tmp>90)
		OCR1B_tmp =90;
		if (OCR1B_tmp<10)
		OCR1B_tmp =10;
		OCR1B=OCR1B_tmp;
	}
}

// ==============================================================================================================
// Hier beginnt das Hauptprogramm "main"
// --------------------------------------------------------------------------------------------------------------

int main (void)
{
	init_BT_CAR_V2_0();			// Das Board wird hier initialisiert
	write_text(0,4, PSTR("READY TO GO!"));	
	wait_1ms(1000);	
	clear_lcd();				// LCD clear
	init_ADC();
	init_RGB();
	init_UART0();
	init_PWM_16Bit_Timer1();
	

	//write_text(0, 0 ,PSTR("JoyX: "));
	//write_text(1, 0 ,PSTR("JoyY: "));
	//write_text(2, 0 ,PSTR("Lich: "));
	//write_text(3, 0, PSTR("DipS: "));
	//write_text(0, 11,PSTR("RxD : "));	
	//write_text(1, 11,PSTR("LED : "));
	//write_text(3, 11,PSTR("time: "));
	while(1)
	{
		DIP_Switch=get_DIP_Switch();
		//wait_1ms(100);
		//write_zahl(0, 5 ,get_ADC_Channel(JOYSTICK_X)>>2,4,0,0);
		//write_zahl(1, 5 ,get_ADC_Channel(JOYSTICK_Y)>>2,4,0,0);
		//write_zahl(2, 5 ,get_ADC_Channel(LICHTSENSOR)>>2,4,0,0);
		//write_zahl(3, 5 ,get_DIP_Switch(),4,0,0);
		//write_zahl(0, 16,Receive_count,4,0,0);
		//write_zahl(1, 16,PINB,4,0,0);
		//write_zahl(3, 16,tick_1s,4,0,0);		
		if (DIP_Switch==1)
		{
			OCR1A=10;
			OCR1B=10;
		}
		if (DIP_Switch==2)
		{
			OCR1A=90;
			OCR1B=90;
		}
		
		write_zahl(0,0,OCR1A,3,0,0);
		write_zahl(1,0,OCR1B,3,0,0);
	}
}









//ISR (USART0_RX_vect) // UART0 Empfangsinterrupt
//{
//
//Receive_count++;
//Data_Array[i] = UDR0;	//Empfangspuffer lesen
//i++;
//
//if (i==sizeof(Data_Array))
//{
//i=0;
//switch(Data_Array[0])
//{
//case 'R': OCR1B=((Data_Array[1]-0x30)*100+(Data_Array[2]-0x30)*10+(Data_Array[3]-0x30)); //Rot
//break;
//case 'G': OCR1A=((Data_Array[1]-0x30)*100+(Data_Array[2]-0x30)*10+(Data_Array[3]-0x30)); //Green
//break;
//case 'B': OCR2B=((Data_Array[1]-0x30)*100+(Data_Array[2]-0x30)*10+(Data_Array[3]-0x30)); //Blau
//break;
//case 'L': PORTB=((Data_Array[1]-0x30)*100+(Data_Array[2]-0x30)*10+(Data_Array[3]-0x30)); //LED Port
//break;
//case 'D': Send_USART(DIP_SWITCH,get_DIP_Switch()); //DIP_Switch
//break;
//case 'X': Send_USART(JOYSTICK_X,get_ADC_Channel(JOYSTICK_X)>>2); //Joystick_X 8-Bit
//break;
//case 'Y': Send_USART(JOYSTICK_Y,get_ADC_Channel(JOYSTICK_Y)>>2); //Joystick_Y 8-Bit
//break;
//case 'S': Send_USART(LICHTSENSOR,get_ADC_Channel(LICHTSENSOR)>>2); //Lichtsensor 8-Bit
//break;
//}
//}
//}

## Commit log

2019-02-27 lu da bueb da isch en zed
2019-02-27 überall hets zed's dra zed's dra zed's dra
2019-02-27 meee infooooos :D
2019-02-27 Erste Dataset Bilder
    Bilder...
2019-02-27 ka was ich da gmacht han ehrlich gseit
2019-02-27 umeprööbelet
2019-02-27 Yolo net Hinzugefügt
2019-03-04 YOLOv3 hinzugefügt
    Erste Tests mit Yolo
2019-03-06 New Trained Yolo
2019-03-13 blabla und so
    tested some thing
2019-03-13 programmiert+python script für kamera
2019-03-13 Neue Trainingsdaen Hinzugefügt
2019-03-18 e chli umeprobiert
2019-03-19 what so ever
2019-03-20 name=robo_boy, Konzept
2019-03-20 readme aktualisiert(wil ich lustig bi)
2019-03-20 paar funktione
    get_tecnical_data oder so
    emergency_stop
    move
2019-03-20 robo_boy wiiter gmacht und funktione gmacht :)
2019-03-30 cleand up yolo
    removed usless files. traind a cupple times. fixed some errors
2019-04-03 ehm... das isch vo letscht wuche gsi... da hemmer glaub es paar testlis gmacht nix wichtigs also
2019-04-03 het jetz e start pos und me cha de joy stick benutze :)
2019-04-10 First GUI
2019-05-15 ich hans githubiert (sagns ma... kennns d muldipremia schon)
2019-05-15 gituuub
2019-05-15 seich
2019-06-05 es paar enderige
2019-06-05 oruzl
2019-06-05 dsfhdf
2019-06-06 get githuubiert
    WAS MACHED DIE ZEDDEL I DE CHISTEEEE?
2019-06-12 addvbhhbLS
    AGERAB
2019-06-12 grid
2019-06-26 5i5ed
2019-06-26 rzfuöv
2019-06-26 kdgkcgjkfghjk
2019-06-26 bt shit
2019-07-03 ahdy
2019-07-03 vuiö
2019-07-03 qefbe
2019-07-03 afu5rstjehsrestrkdzturtr
2019-08-20 mir hend uart bro
2019-08-20 adsd
2019-08-21 dfgdfg
2019-08-27 rwer
2019-09-03 dfbdaf
2019-09-03 englisch teil done
2019-09-03 OKE.py und Dateien veränderungen
    OKE.py updated und auf Raspi angepasst.
    UART kommunikation etabliert.
    unnötige datasamples entfernt
2019-09-03 asdas
2019-09-10 wefgw
2019-09-10 kopiert
2019-09-10 Little Clean up
2019-09-13 sdfsd
2019-09-23 shrt
2019-09-24 Update for Mechatronik days
2019-09-24 ready für TodT
2019-09-26 Raspi Update
2019-10-01 Dataset update
    New Training session with Yolo net
2019-10-01 print fertig
2019-10-22 print stuff i guess
2019-10-22 printv2.0
2019-10-29 stkrtstjkmt,zh
2019-10-29 Start of Presentation
    Presentation Inizialisiert
2019-11-07 Yolo
2019-11-12 Presentation
2019-11-26 Fusion Haaaaaa
2019-11-26 Bump pillow in /KI/Data_set/Labelbox/exporters/coco-exporter
    Bumps [pillow](https://github.com/python-pillow/Pillow) from 6.1.0 to 6.2.0.
    - [Release notes](https://github.com/python-pillow/Pillow/releases)
    - [Changelog](https://github.com/python-pillow/Pillow/blob/master/CHANGES.rst)
    - [Commits](https://github.com/python-pillow/Pillow/compare/6.1.0...6.2.0)
2019-12-03 Things added
2019-12-10 Dinge Geändert
2019-12-17 geschmeus
2020-02-18 yeees
2020-05-29 pijilj
2020-06-16 tzdu
2020-06-16 clean up
2022-12-08 Bump certifi in /KI/Data_set/Labelbox/exporters/coco-exporter
    Bumps [certifi](https://github.com/certifi/python-certifi) from 2019.6.16 to 2022.12.7.
    - [Release notes](https://github.com/certifi/python-certifi/releases)
    - [Commits](https://github.com/certifi/python-certifi/compare/2019.06.16...2022.12.07)
    ---
    updated-dependencies:
    - dependency-name: certifi

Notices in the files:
parts and their libraries:
con-molex-usb: (C) 2014 Tomasz Boleslaw CEDRO, cederom@tlen.pl, http://www.tomek.cedro.info.
